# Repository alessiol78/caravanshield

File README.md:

# caravanshield
Caravan/Motorhome battery manager shield for Raspberry Pi W Zero

Schematics and PCB board are made in Eagle 8.6.3. See [board/](board) folder.
In the folder yoy can found [schematic](board/schema.pdf) in PDF version, 3D-render for the PCB and Gebers files.

The firmware and software for Android is made with Qt5.9.

In the folder [raspberry/](raspberry/ubatmanager) you can found the firmware for Rapsberry Pi.

In the folder android/ you can found the source for the Android APK.

In the folder [remotelcd/](remotelcd) you can found the OledLCD emulation for developing the rapberry firmware on Linux PC (x86_64).

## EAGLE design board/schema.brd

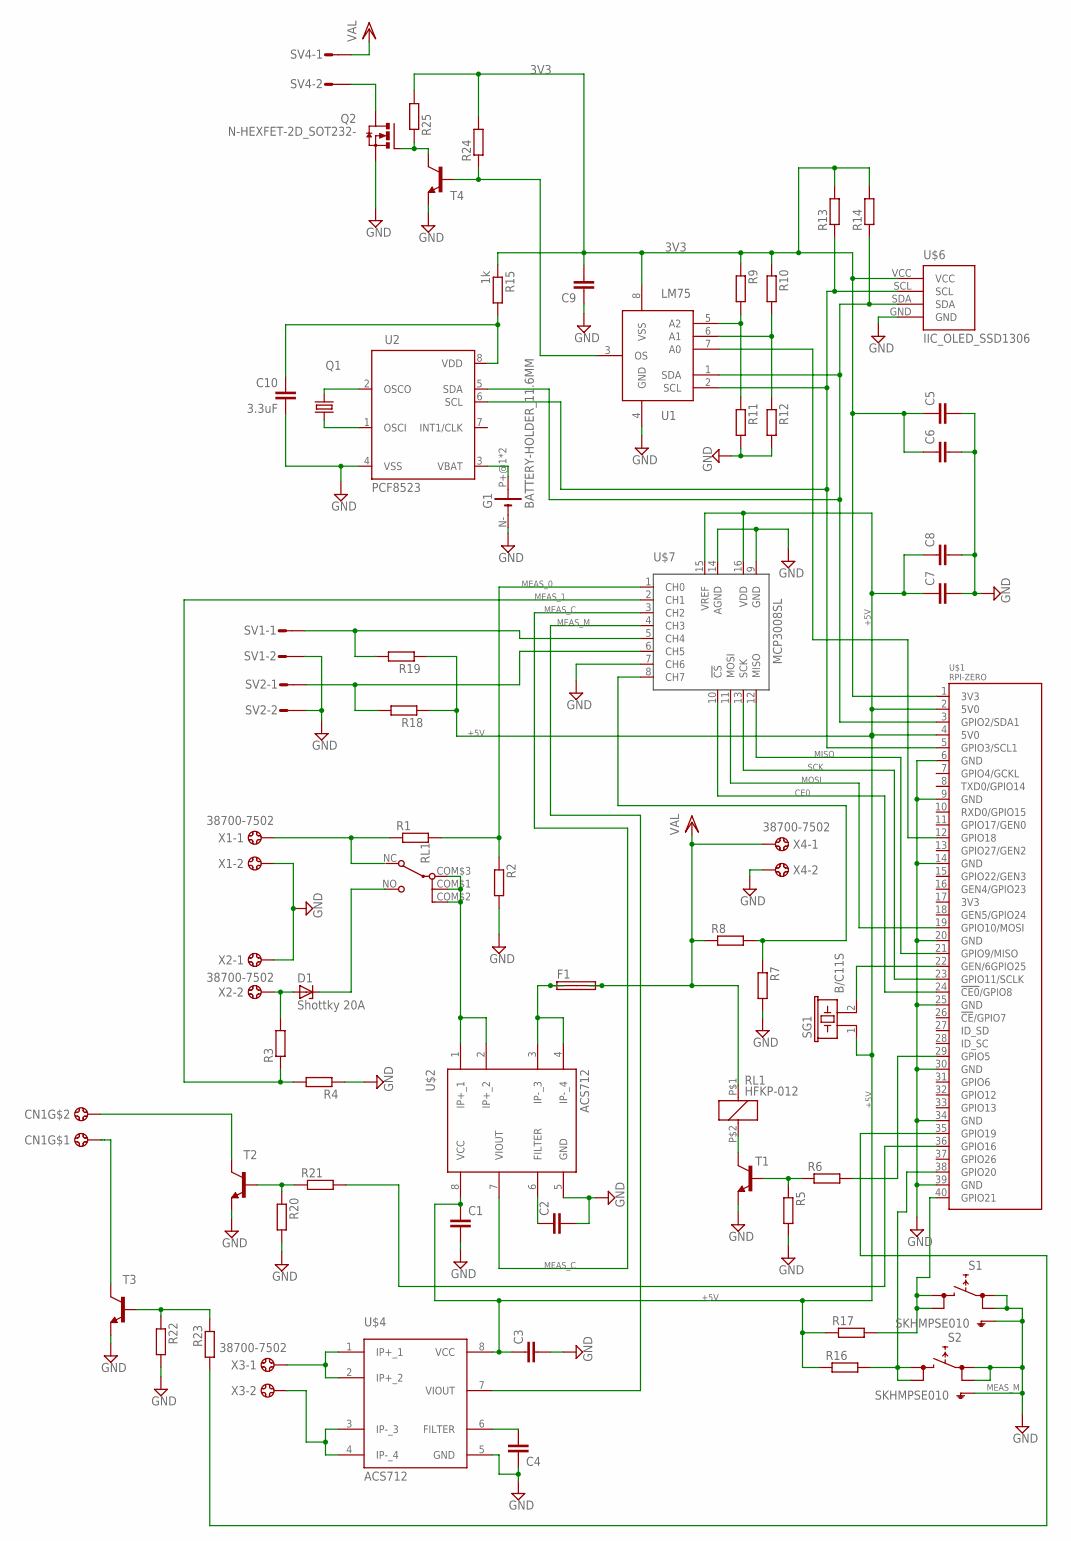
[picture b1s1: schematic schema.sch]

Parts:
C1, C2, C3, C4, C5, C6, C7, C8, C9: CC0603; C0603
C10: 3.3uF; C0603
CN1: CON_VITE_2POS; CN02
D1: Shottky 20A; C1702-15
F1: SHK20Q
G1: BATTERY-HOLDER_11.6MM; CELL_RETAINER_11.6MM
Q1: KX-327-S; 8.2X3.8
Q2: N-HEXFET-2D_SOT232-; SOT223
R1, R2, R3, R4, R5, R6, R7, R8, R9, R10, R11, R12, R13, R14, R16, R17, R18, R19, R20, R21, R22, R23, R24, R25: RR0603; R0603
R15: 1k; R0603
RL1: HFKP-012; HFKP-1X5
S1, S2: SKHMPSE010; SKHMPXE010
SG1: B/C11S
SV1, SV2, SV4: S02P
T1, T2, T3, T4: -NPN-SOT23-EBC; SOT23-EBC
U1: LM75; SO08
U2: PCF8523; SO08-IRF
U$1: RPI-ZERO; RASPBERRYPI_V13_J8
U$2, U$4: ACS712; SOIC8
U$6: IIC_OLED_SSD1306; OLED-SSD1306
U$7: MCP3008SL; SO16
X1, X2, X3, X4: 38700-7502

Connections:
3V3: C5.1, C6.1, C9.2, R9.1, R10.1, R13.2, R14.2, R15.1, R24.2, R25.2, U1.8 (VSS), U$1.1 (3V3), U$6.VCC
+5V: C1.1, C3.1, C7.1, C8.1, R16.1, R17.1, R18.1, R19.1, SG1.1, U$1.2 (5V0), U$1.4 (5V0), U$2.8 (VCC), U$4.8 (VCC), U$7.15 (VREF), U$7.16 (VDD)
CE0: U$1.24 (!CE0!/GPIO8), U$7.10 (!CS)
GND: C1.2, C2.2, C3.2, C4.1, C5.2, C6.2, C7.2, C8.2, C9.1, C10.2, G1.N- (-), Q2.3 (S), R2.2, R4.1, R5.2, R7.2, R11.2, R12.2, R20.2, R22.2, S1.1 (1.1), S1.2 (1.2), S1.5 (SH), S2.1 (1.1), S2.2 (1.2), S2.5 (SH), SV1.2, SV2.2, T1.E, T2.E, T3.E, T4.E, U1.4 (GND), U2.4 (VSS), U$1.6 (GND), U$1.9 (GND), U$1.14 (GND), U$1.20 (GND), U$1.25 (GND), U$1.30 (GND), U$1.34 (GND), U$1.39 (GND), U$2.5 (GND), U$4.5 (GND), U$6.GND, U$7.7 (CH6), U$7.9 (GND), U$7.14 (AGND), X1.2, X2.1, X4.2
MEAS_0: R1.2, R2.1, U$7.1 (CH0)
MEAS_1: R3.1, R4.2, U$7.2 (CH1)
MEAS_C: U$2.7 (VIOUT), U$7.3 (CH2)
MEAS_M: U$4.7 (VIOUT), U$7.4 (CH3)
MEAS_O: R7.1, R8.2, U$7.8 (CH7)
MISO: U$1.21 (GPIO9/MISO), U$7.12 (MISO)
MOSI: U$1.19 (GPIO10/MOSI), U$7.11 (MOSI)
unnamed: R1.1, RL1.NC (O), X1.1
unnamed: R9.2, R11.1, U1.5 (A2)
unnamed: RL1.COM$1 (P1), RL1.COM$2 (P2), RL1.COM$3 (P3), U$2.1 (IP+_1), U$2.2 (IP+_2)
unnamed: D1.A, R3.2, X2.2
unnamed: D1.C, RL1.NO (S)
unnamed: C4.2, U$4.6 (FILTER)
unnamed: F1.1A, F1.1B, U$2.3 (IP-_3), U$2.4 (IP-_4)
unnamed: U$4.1 (IP+_1), U$4.2 (IP+_2), X3.1
unnamed: C2.1, U$2.6 (FILTER)
unnamed: U$4.3 (IP-_3), U$4.4 (IP-_4), X3.2
unnamed: R5.1, R6.1, T1.B
unnamed: R10.2, R12.1, U1.6 (A1)
unnamed: RL1.P$2 (2), T1.C
unnamed: R6.2, U$1.29 (GPIO5)
unnamed: U1.7 (A0), U$1.12 (GPIO18)
unnamed: SG1.2, U$1.22 (GEN/6GPIO25)
unnamed: G1.P+@1 (+), G1.P+@2 (+), U2.3 (VBAT)
unnamed: Q1.4 (2), U2.1 (OSCI)
unnamed: Q1.1, U2.2 (OSCO)
unnamed: C10.1, R15.2, U2.8 (VDD)
unnamed: R16.2, S2.3 (2.1), S2.4 (2.2), U$1.38 (GPIO20)
unnamed: R17.2, S1.3 (2.1), S1.4 (2.2), U$1.40 (GPIO21)
unnamed: CN1.P$2, T2.C
unnamed: R20.1, R21.1, T2.B
unnamed: R19.2, SV1.1, U$7.5 (CH4)
unnamed: R18.2, SV2.1, U$7.6 (CH5)
unnamed: R21.2, U$1.36 (GPIO16)
unnamed: CN1.P$1, T3.C
unnamed: R22.1, R23.1, T3.B
unnamed: R24.1, T4.B, U1.3 (OS)
unnamed: R23.2, U$1.35 (GPIO19)
unnamed: Q2.1 (G), R25.1, T4.C
unnamed: Q2.2 (D), Q2.4 (D), SV4.2
SCK: U$1.23 (GPIO11/SCLK), U$7.13 (SCK)
SCL: R13.1, U1.2 (SCL), U2.6 (SCL), U$1.5 (GPIO3/SCL1), U$6.SCL
SDA: R14.1, U1.1 (SDA), U2.5 (SDA), U$1.3 (GPIO2/SDA1), U$6.SDA
VDD: F1.2A, F1.2B, R8.1, RL1.P$1 (1), SV4.1, X4.1

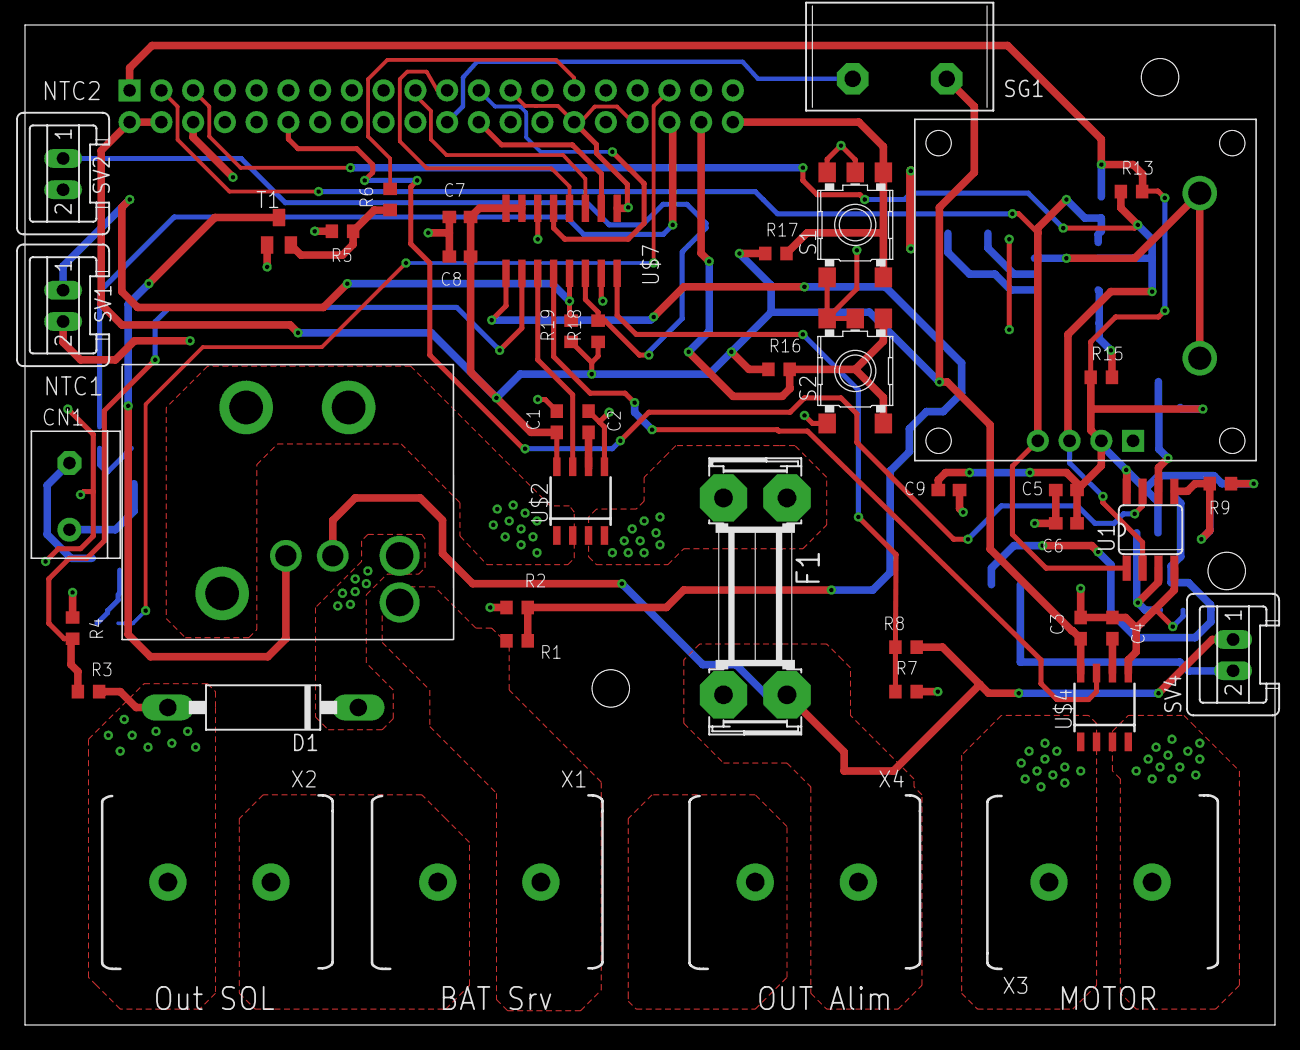
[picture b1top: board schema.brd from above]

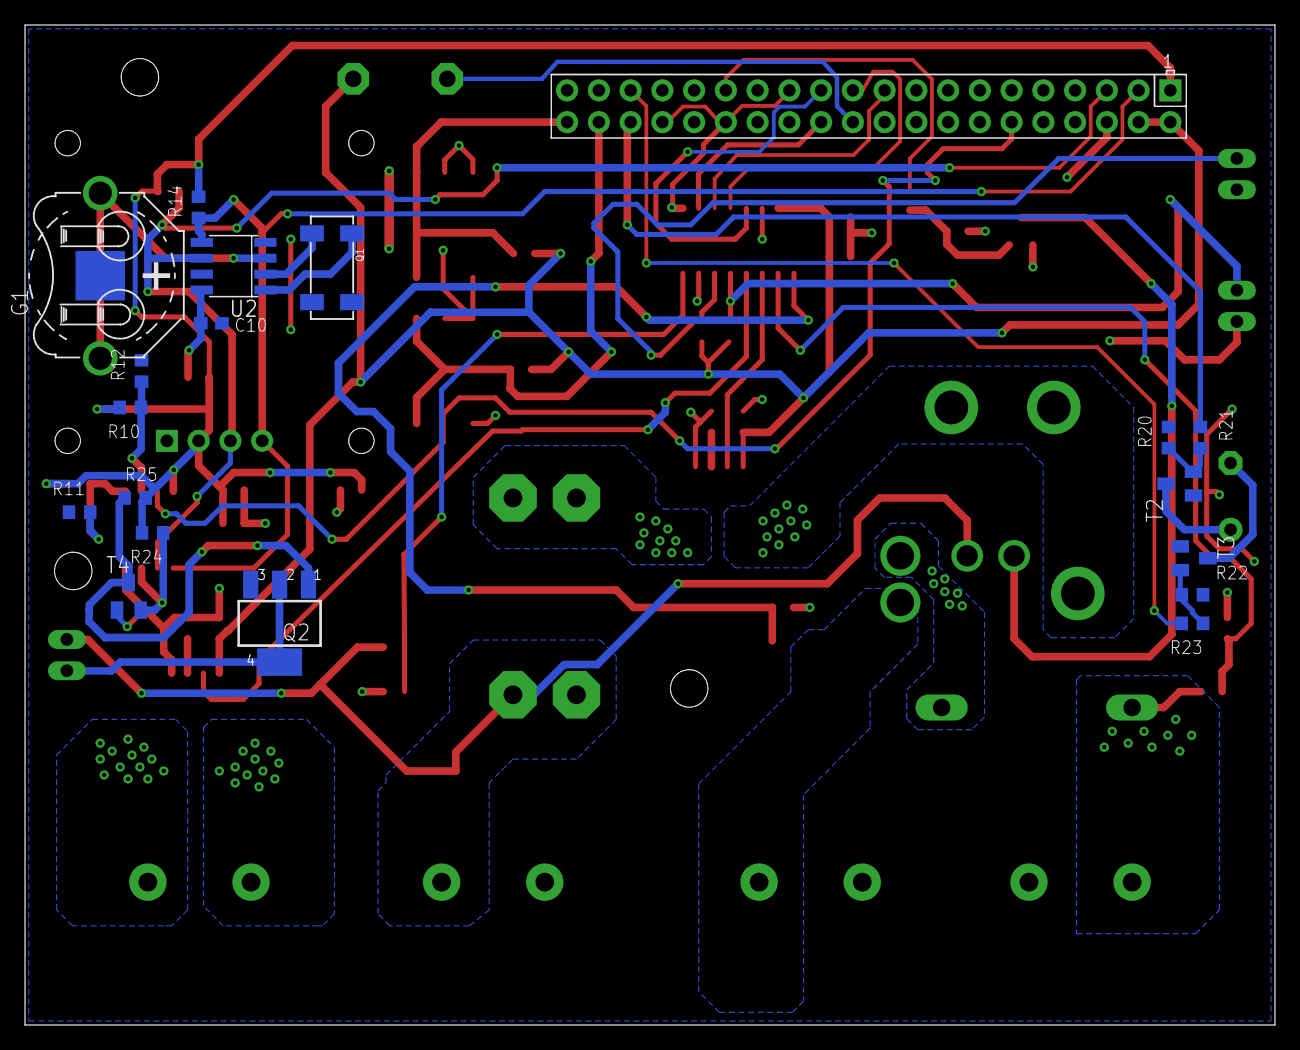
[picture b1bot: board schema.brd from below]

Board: 2 copper layers, 100.0 x 80.0 mm, 63 parts (19 on the bottom side), 48 nets.

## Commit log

2018-03-13 added board (schematic plus pcb)
2018-03-13 added firmware and lcd emulator for x86
2018-03-14 added schema
2018-03-14 link in readme
2018-03-14 fix link in readme
2018-03-14 add new link in readme
2018-03-22 aggiunti grafici v ed i e pulsanti a remotelcd
2018-03-24 modifiche per adeguamento emulatore e bluetooth ble
2018-03-25 aggiunto progetto android
2018-03-25 bozza di configure params on myandroid app
2018-03-30 fix rotate display
2018-03-31 switch relay strategy
2018-04-09 bozza lettura sensore lm75
2018-04-20 prove con sensore di temperatura interno

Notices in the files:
parts and their libraries:
crystal-geyer_V1_0: Copyright: Geyer-Electronic
